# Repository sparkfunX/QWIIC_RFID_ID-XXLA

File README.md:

Sparkfun Qwiic RFID ID-XXLA
========================================

[*SparX Qwiic Keypad (SPX-14867)*](https://www.sparkfun.com/products/14867)

The Qwiic RFID ID-XXLA is a simple board that pairs with the ID-3LA, ID-12LA, ID-20LA, RFID modules. Included with the product is the ID-12LA and three RFID 125Khz cards as a full kit to get you started integrating an I2C RFID solution into your project. Utilizing the onboard ATtiny84A, the Qwiic RFID takes the six byte ID tag of your 125Khz RFID card, attaches a time stamp to it, and puts it onto a stack that holds up to 20 unique RFID scans at any given time. This information is easy to get at with some simple I2C commands and weve included some example code that shows you just how to do it using the broken out interrupt pin. Weve also broken out two antennae pins that should only be used with the smaller ID-3LA.

The Qwiic RFID has a buzzer and LED that indicates that card has been scanned. Weve included a jumper to disconnect the buzzer, a jumper for the I2C pull-up resistors, an interrupt jumper, and finally an address jumper. The Qwiic RFID comes fully decked out in Qwiic connectors, no need to solder a thing, just plug it in and start scanning!

We do not plan to regularly produce SparkX products so get them while theyre hot!

Repository Contents
-------------------

* **/Examples** - A number of examples to show how to read buttons with time, change the I2C address and scan for I2C devices
* **/Firmware** - The core sketch that runs Qwiic RFID ID-XXLA
* **/Hardware** - Eagle design files (.brd, .sch)

License Information
-------------------

This product is _**open source**_! 

Please review the LICENSE.md file for license information. 

If you have any questions or concerns on licensing, please contact techsupport@sparkfun.com.

Please use, reuse, and modify these files as you see fit. Please maintain attribution to SparkFun Electronics and release any derivative under the same license.

Distributed as-is; no warranty is given.

- Your friends at SparkFun.

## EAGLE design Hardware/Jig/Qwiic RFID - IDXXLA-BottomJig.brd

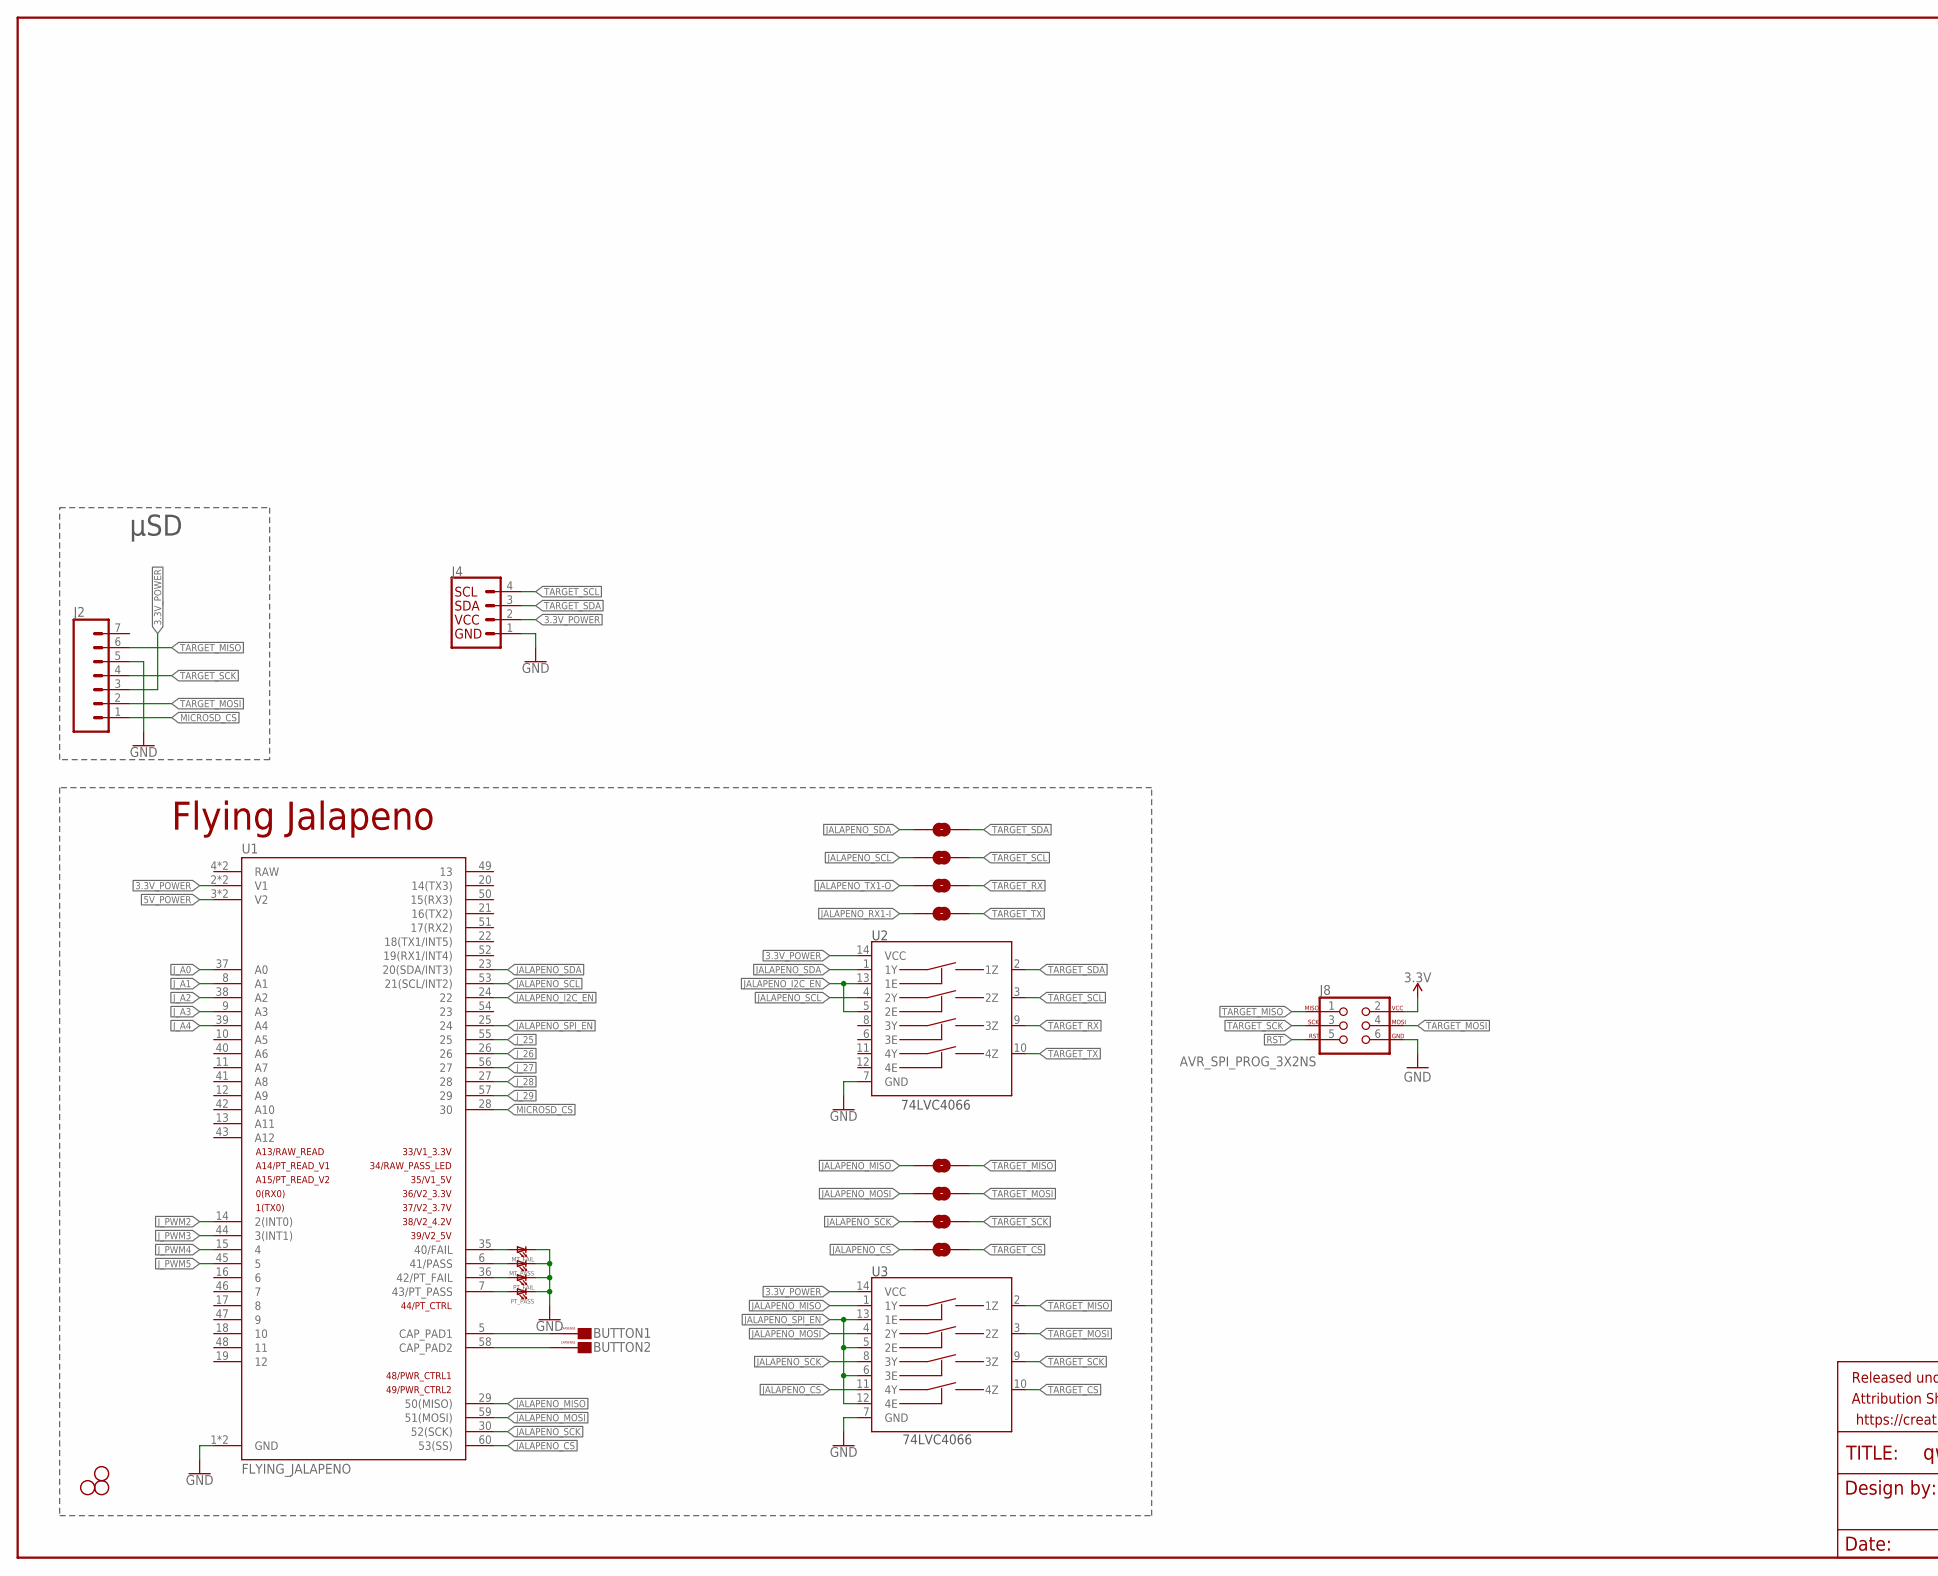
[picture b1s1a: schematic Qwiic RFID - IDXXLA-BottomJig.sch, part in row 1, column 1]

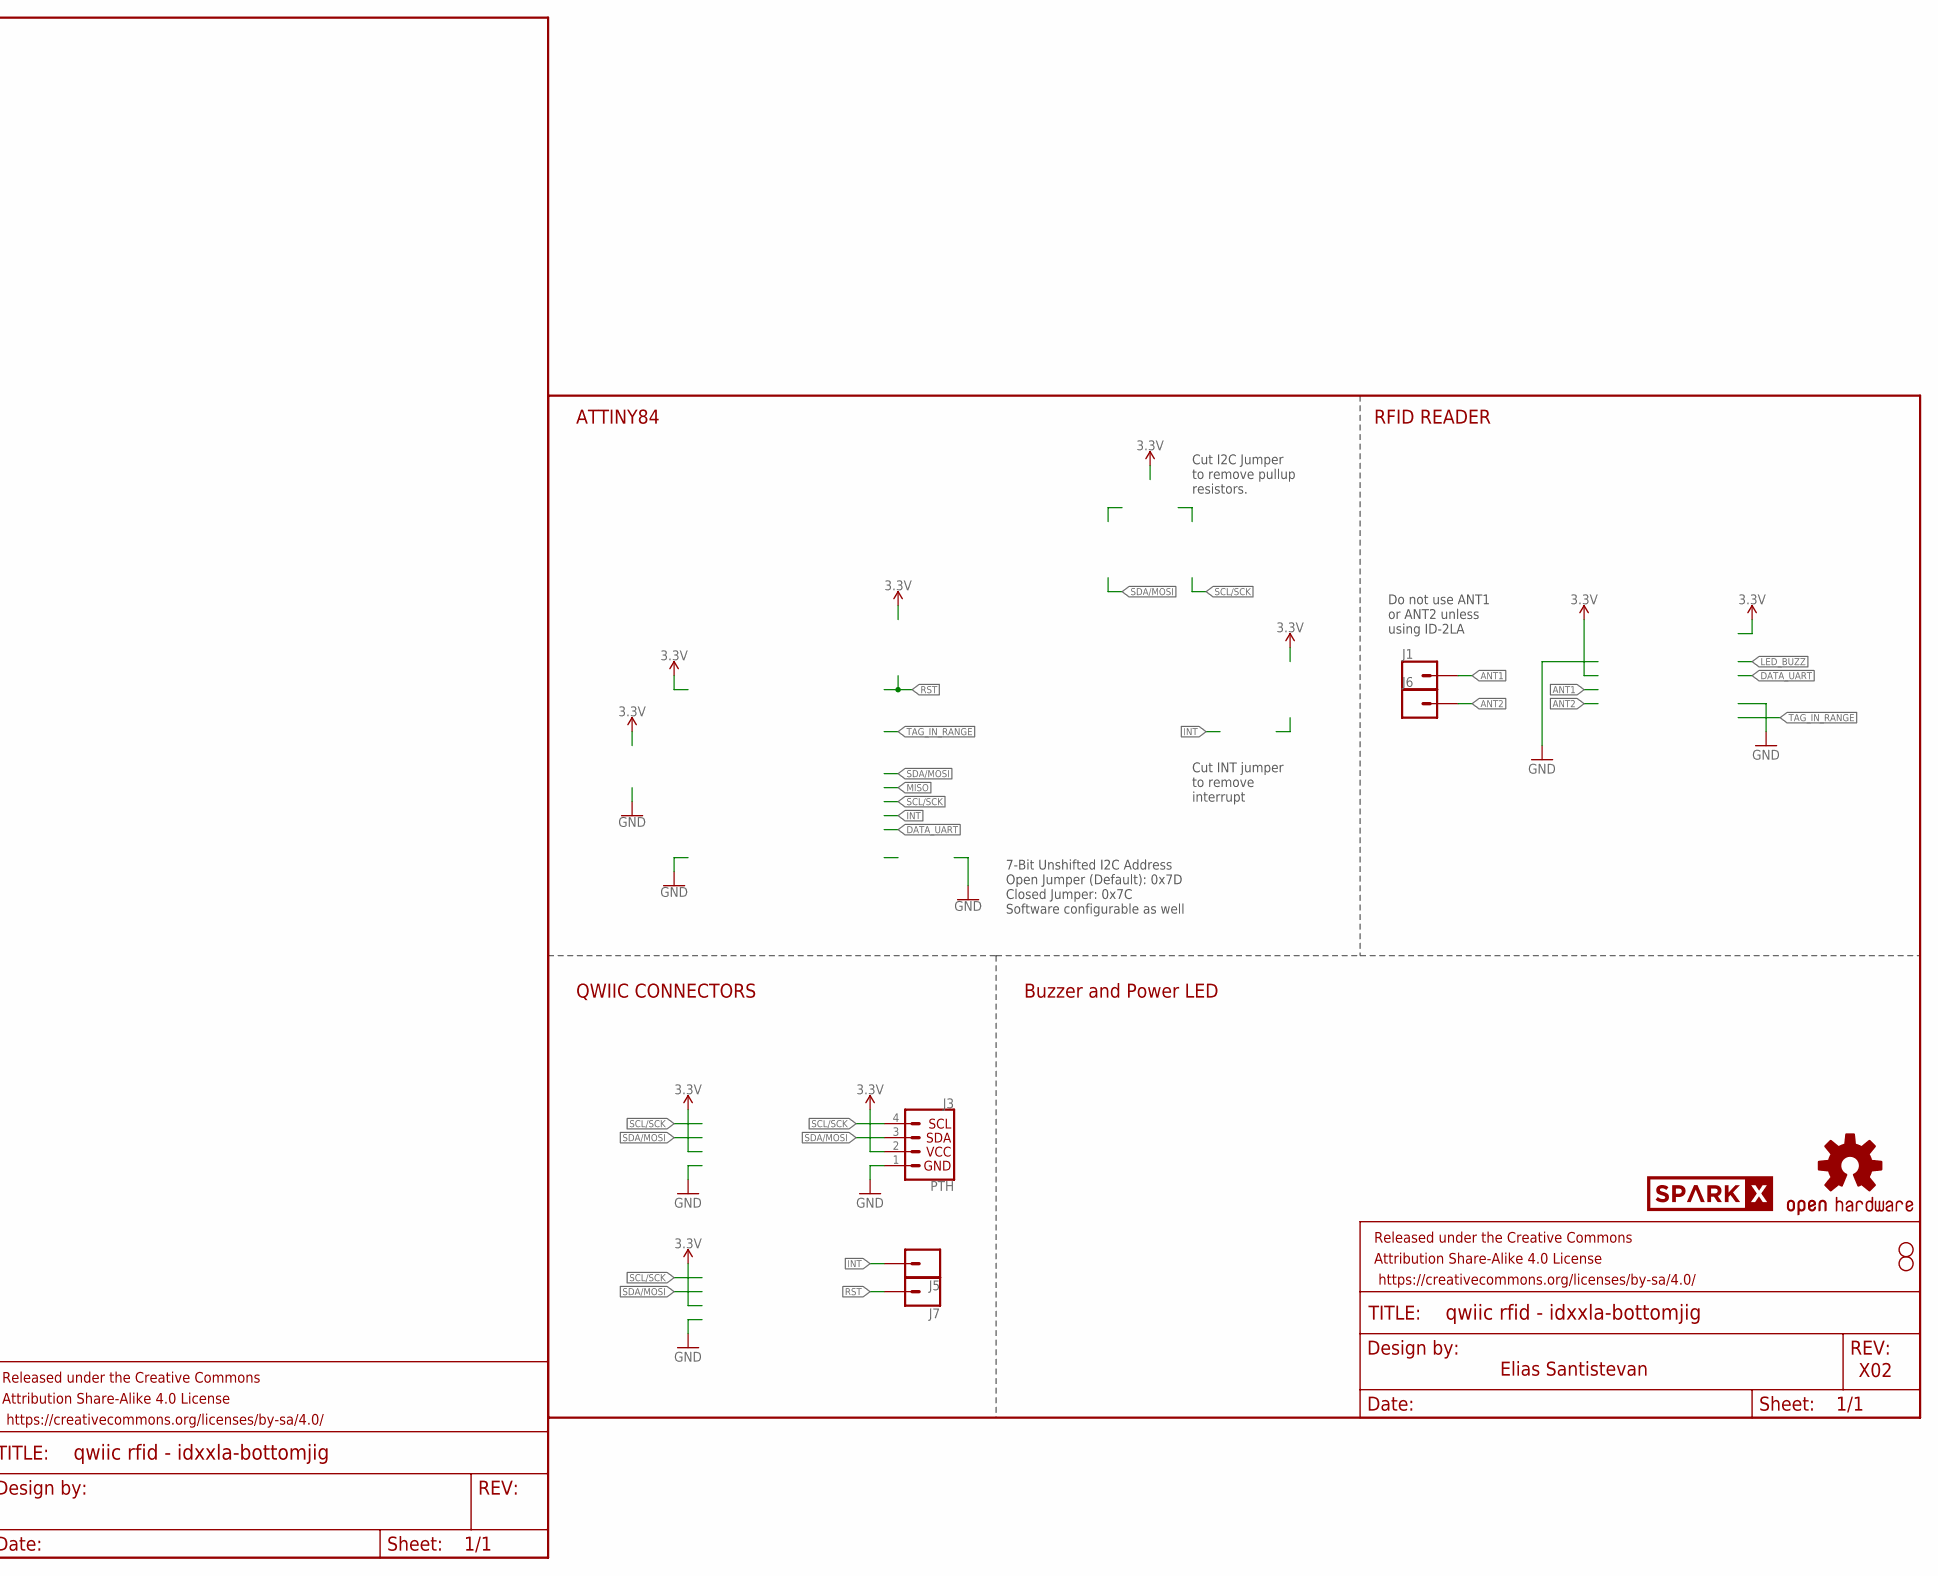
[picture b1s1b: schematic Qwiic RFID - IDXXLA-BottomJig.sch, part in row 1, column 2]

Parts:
BUTTON1, BUTTON2: CAPSENSE_BUTTON_PAD_ONLY; CAPSENSE_BUTTON_PADS_ONLY
FRAME1: FRAME-LETTER; CREATIVE_COMMONS
FRAME2: FRAME-LEDGER; CREATIVE_COMMONS
H1, H3, H4: STAND-OFF
J1, J5, J6, J7: CONN_01PTH_NO_SILK_YES_STOP; 1X01_NO_SILK
J2: CONN_07; 1X07
J3: PTH; 1X04_NO_SILK
J4: QWIIC_CONNECTORJS-1MM; 1X04_1MM_RA
J8: AVR_SPI_PROG_3X2NS; 2X3-NS
JP3, JP4: STAND-OFF
J_SCL, J_SCL1, J_SCL2, J_SCL3, J_SCL4, J_SCL5: JUMPER-SMT_2_NO_NO-SILK; SMT-JUMPER_2_NO_NO-SILK
J_SDA, J_SDA1: JUMPER-SMT_2_NO_NO-SILK; SMT-JUMPER_2_NO_NO-SILK
LOGO1: OSHW-LOGOMINI; OSHW-LOGO-MINI
MT_FAIL: LED1206; LED-1206
MT_PASS: LED1206; LED-1206
PT_FAIL: LED1206; LED-1206
PT_PASS: LED1206; LED-1206
U1: FLYING_JALAPENO; FLYING_JALAPENO_V3_M
U2, U3: 74LVC4066; SO14
U$4: SPARKX-LOGO3; SPARKX-SMALL

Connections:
3.3V: J3.2 (VCC), J8.2
3.3V_POWER: J2.3, J4.2, U1.2 (V1), U1.32 (V1), U2.14 (VCC), U3.14 (VCC)
5V_POWER: U1.3 (V2), U1.33 (V2)
!INT: J5.1
!RST: J7.1, J8.5
ANT1: J1.1
ANT2: J6.1
BUTTON1: BUTTON1.CAPSENSE_PAD, U1.5 (CAP_PAD1)
BUTTON2: BUTTON2.CAPSENSE_PAD, U1.58 (CAP_PAD2)
GND: J2.5, J3.1 (GND), J4.1, J8.6, MT_FAIL.C, MT_PASS.C, PT_FAIL.C, PT_PASS.C, U1.1 (GND), U1.31 (GND), U2.7 (GND), U3.7 (GND)
JALAPENO_CS: J_SDA1.1, U1.60 (53(SS)), U3.11 (4Y)
JALAPENO_I2C_EN: U1.24 (22), U2.5 (2E), U2.13 (1E)
JALAPENO_MISO: J_SCL5.1, U1.29 (50(MISO)), U3.1 (1Y)
JALAPENO_MOSI: J_SCL3.1, U1.59 (51(MOSI)), U3.4 (2Y)
JALAPENO_RX1-I: J_SDA.1
JALAPENO_SCK: J_SCL4.1, U1.30 (52(SCK)), U3.8 (3Y)
JALAPENO_SCL: J_SCL.1, U1.53 (21(SCL/INT2)), U2.4 (2Y)
JALAPENO_SDA: J_SCL2.1, U1.23 (20(SDA/INT3)), U2.1 (1Y)
JALAPENO_SPI_EN: U1.25 (24), U3.5 (2E), U3.6 (3E), U3.12 (4E), U3.13 (1E)
JALAPENO_TX1-O: J_SCL1.1
J_25: U1.55 (25)
J_26: U1.26
J_27: U1.56 (27)
J_28: U1.27 (28)
J_29: U1.57 (29)
J_A0: U1.37 (A0)
J_A1: U1.8 (A1)
J_A2: U1.38 (A2)
J_A3: U1.9 (A3)
J_A4: U1.39 (A4)
J_PWM2: U1.14 (2(INT0))
J_PWM3: U1.44 (3(INT1))
J_PWM4: U1.15 (4)
J_PWM5: U1.45 (5)
MICROSD_!CS!: J2.1, U1.28 (30)
MT_FAIL: MT_FAIL.A, U1.35 (40/FAIL)
MT_PASS: MT_PASS.A, U1.6 (41/PASS)
PT_FAIL: PT_FAIL.A, U1.36 (42/PT_FAIL)
PT_PASS: PT_PASS.A, U1.7 (43/PT_PASS)
SCL/SCK: J3.4 (SCL)
SDA/MOSI: J3.3 (SDA)
TARGET_CS: J_SDA1.2, U3.10 (4Z)
TARGET_MISO: J2.6, J8.1, J_SCL5.2, U3.2 (1Z)
TARGET_MOSI: J2.2, J8.4, J_SCL3.2, U3.3 (2Z)
TARGET_RX: J_SCL1.2, U2.9 (3Z)
TARGET_SCK: J2.4, J8.3, J_SCL4.2, U3.9 (3Z)
TARGET_SCL: J4.4, J_SCL.2, U2.3 (2Z)
TARGET_SDA: J4.3, J_SCL2.2, U2.2 (1Z)
TARGET_TX: J_SDA.2, U2.10 (4Z)

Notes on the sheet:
X02
Buzzer and Power LED
RFID READER
ATTINY84
QWIIC CONNECTORS
Elias Santistevan
7-Bit Unshifted I2C Address Open Jumper (Default): 0x7D Closed Jumper: 0x7C Software configurable as well
Cut INT jumper to remove interrupt
Cut I2C Jumper to remove pullup resistors.
Do not use ANT1 or ANT2 unless using ID-2LA
Flying Jalapeno
μSD

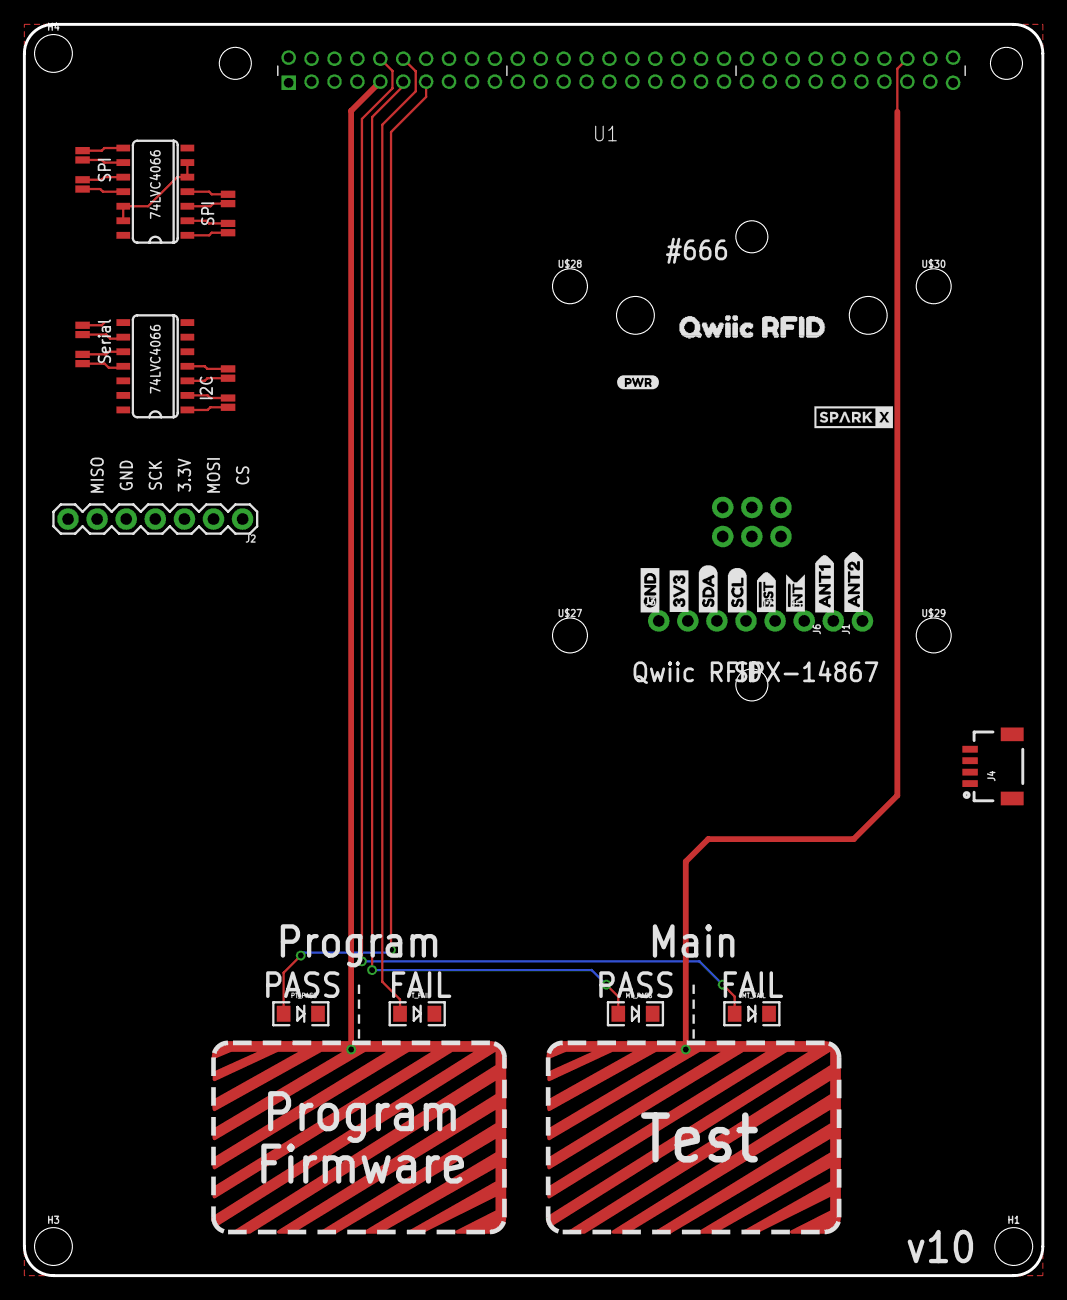
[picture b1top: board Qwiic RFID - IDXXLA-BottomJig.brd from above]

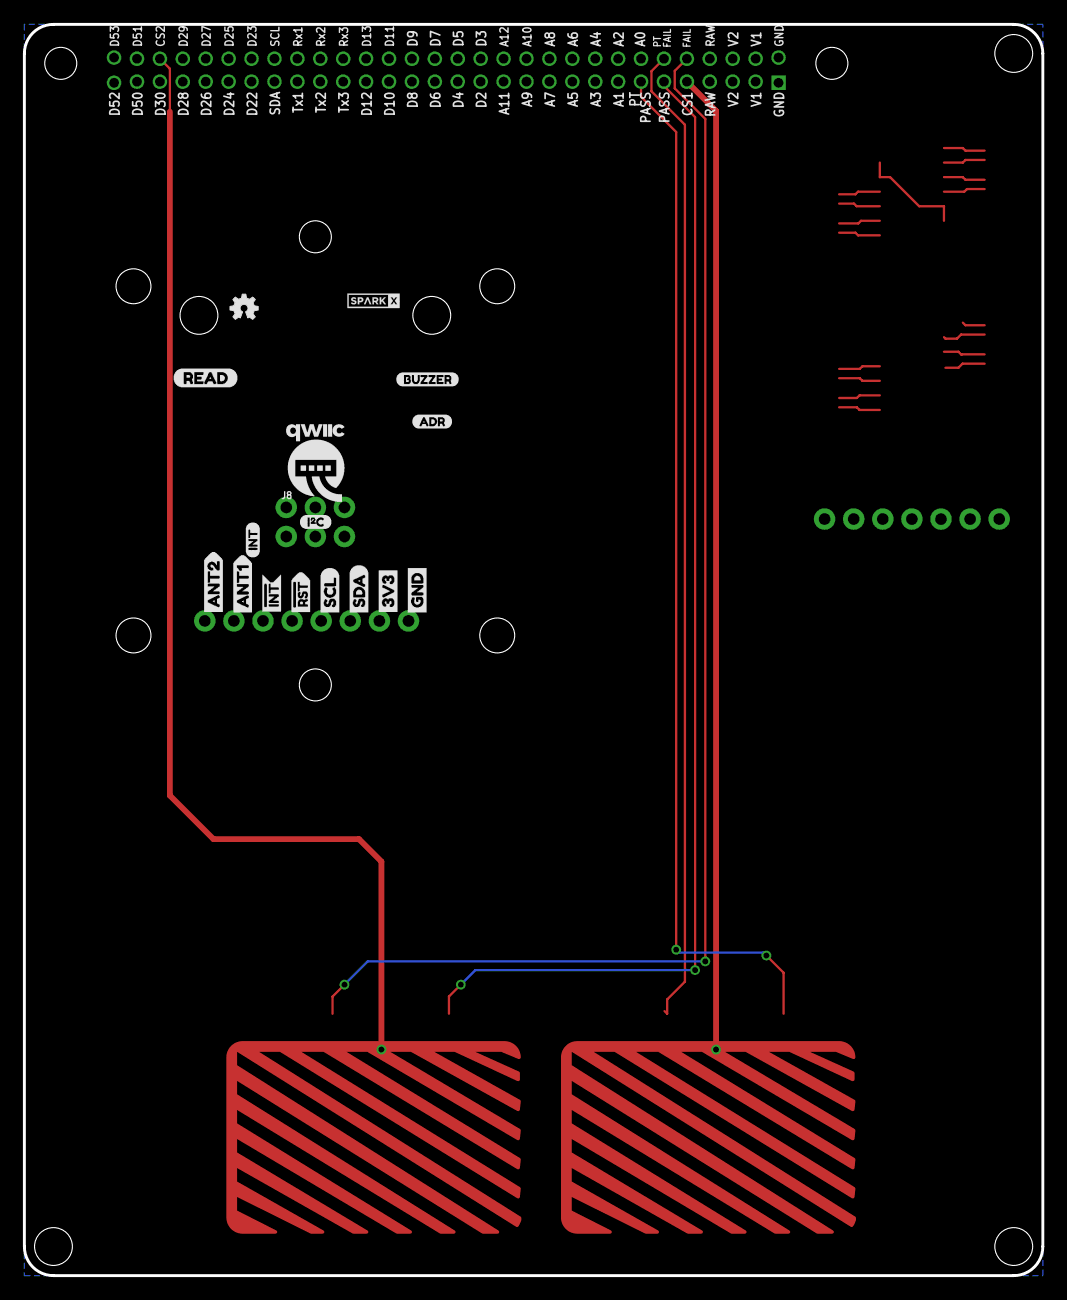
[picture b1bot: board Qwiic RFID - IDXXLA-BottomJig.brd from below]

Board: 2 copper layers, 88.9 x 109.2 mm, 65 parts (17 on the bottom side), 28 nets.

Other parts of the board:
U$1: SPARKX-TINY
U$2: I_SUPER2_C-()-03
U$3, U$17: ANT20
U$5, U$26: RST#-[>
U$6, U$23: SDA-[)
U$7, U$22: SCL-[)
U$8: QWIIC-LOGO-MEDIUM
U$9, U$25: GND-04
U$10, U$24: 3V3-04
U$11, U$21: INT#-[<
U$12: ADR0
U$13: INT0
U$14: PWR-()-03
U$15: BUZZER0
U$16, U$20: ANT10
U$18: READ0
U$19: QWIIC_RFID0
U$27, U$28, U$29, U$30: STAND-OFF-TIGHT
U$31, U$32: NUBBIN_LOCKER

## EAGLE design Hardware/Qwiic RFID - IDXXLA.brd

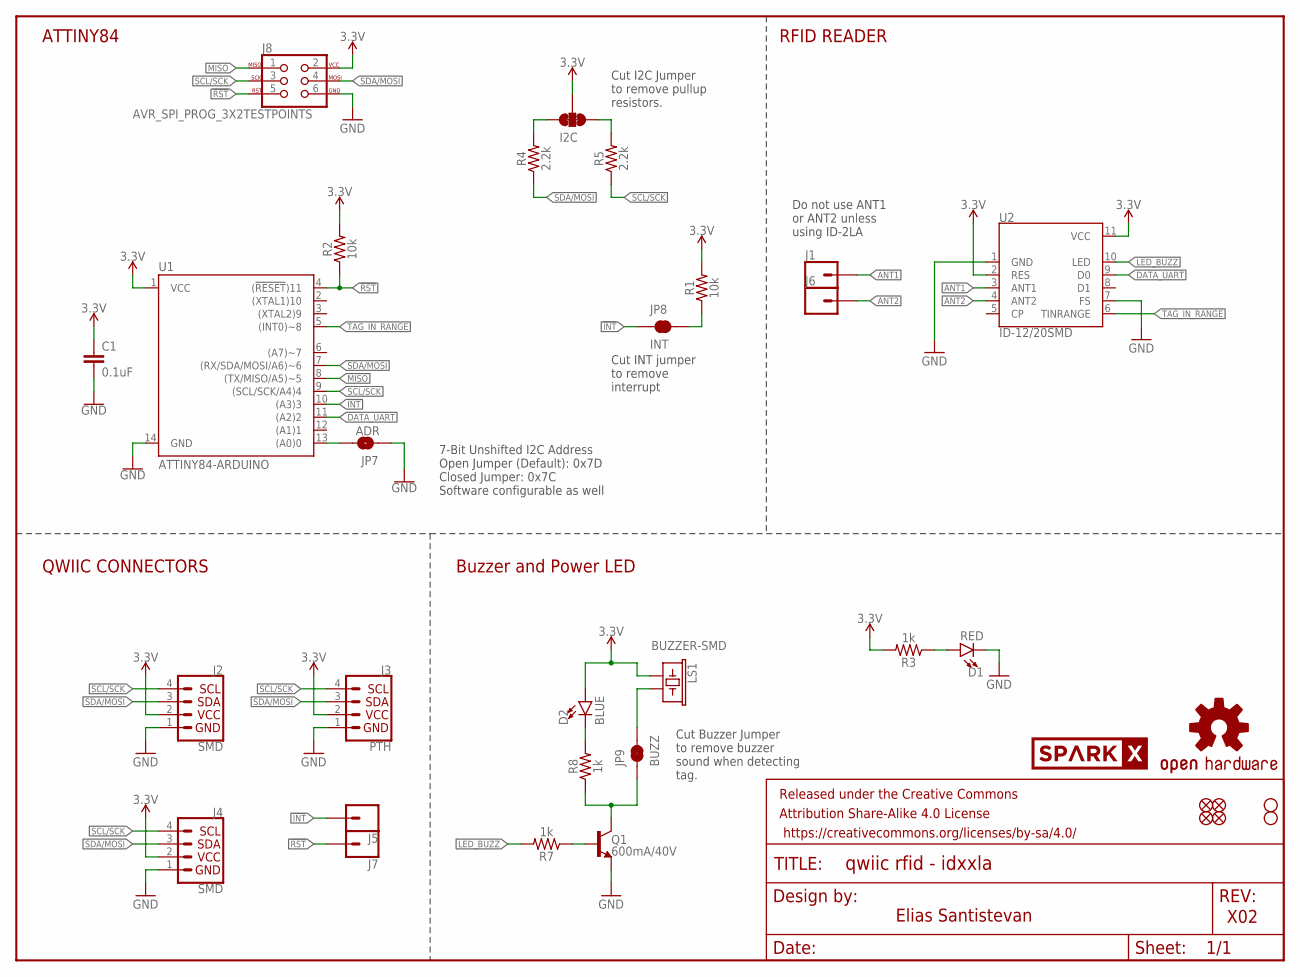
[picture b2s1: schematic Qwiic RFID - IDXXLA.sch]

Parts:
C1: 0.1uF; 0603
D1: RED; LED-0603
D2: BLUE; LED-0603
FRAME1: FRAME-LETTER; CREATIVE_COMMONS
I2C: JUMPER-SMT_3_2-NC_TRACE_SILK; SMT-JUMPER_3_2-NC_TRACE_SILK
J1, J5, J6, J7: CONN_01PTH_NO_SILK_YES_STOP; 1X01_NO_SILK
J2, J4: SMD; 1X04_1MM_RA
J3: PTH; 1X04_NO_SILK
J8: AVR_SPI_PROG_3X2TESTPOINTS; 2X3_TEST_POINTS
JP1, JP2, JP5, JP6: FIDUCIALUFIDUCIAL; MICRO-FIDUCIAL
JP3, JP4: STAND-OFF
JP7: ADR; SMT-JUMPER_2_NO_SILK
JP8: INT; SMT-JUMPER_2_NC_TRACE_SILK
JP9: BUZZ; SMT-JUMPER_2_NC_TRACE_SILK
LOGO1: OSHW-LOGOMINI; OSHW-LOGO-MINI
LS1: BUZZER-SMD; BUZZER-CCV
Q1: 600mA/40V; SOT23-3
R1, R2: 10k; 0603
R3, R7, R8: 1k; 0603
R4, R5: 2.2k; 0603
U1: ATTINY84-ARDUINO; SO14
U2: ID-12/20SMD; ID-12_SMD
U$4: SPARKX-LOGO3; SPARKX-SMALL

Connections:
3.3V: C1.1, D2.A, I2C.2, J2.2 (VCC), J3.2 (VCC), J4.2 (VCC), J8.2, LS1.+ (1), R1.2, R2.2, R3.2, U1.1 (VCC), U2.2 (RES), U2.11 (VCC)
!INT: J5.1, JP8.1, U1.10 ((A3)3)
!RST: J7.1, J8.5, R2.1, U1.4 ((!RESET!)11)
ANT1: J1.1, U2.3 (ANT1)
ANT2: J6.1, U2.4 (ANT2)
DATA_UART: U1.11 ((A2)2), U2.9 (D0)
GND: C1.2, D1.C, J2.1 (GND), J3.1 (GND), J4.1 (GND), J8.6, JP7.1, Q1.2 (E), U1.14 (GND), U2.1 (GND), U2.7 (FS)
LED_BUZZ: R7.2, U2.10 (LED)
MISO: J8.1, U1.8 ((TX/MISO/A5)~5)
unnamed: I2C.1, R5.2
unnamed: I2C.3, R4.2
unnamed: D1.A, R3.1
unnamed: JP8.2, R1.1
unnamed: D2.C, R8.2
unnamed: JP7.2, U1.13 ((A0)0)
unnamed: Q1.1 (B), R7.1
unnamed: JP9.1, Q1.3 (C), R8.1
unnamed: JP9.2, LS1.- (2)
SCL/SCK: J2.4 (SCL), J3.4 (SCL), J4.4 (SCL), J8.3, R5.1, U1.9 ((SCL/SCK/A4)4)
SDA/MOSI: J2.3 (SDA), J3.3 (SDA), J4.3 (SDA), J8.4, R4.1, U1.7 ((RX/SDA/MOSI/A6)~6)
TAG_IN_RANGE: U1.5 ((INT0)~8), U2.6 (TINRANGE)

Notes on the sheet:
X02
Buzzer and Power LED
RFID READER
ATTINY84
QWIIC CONNECTORS
Elias Santistevan
7-Bit Unshifted I2C Address Open Jumper (Default): 0x7D Closed Jumper: 0x7C Software configurable as well
Cut Buzzer Jumper to remove buzzer sound when detecting tag.
Cut INT jumper to remove interrupt
Cut I2C Jumper to remove pullup resistors.
Do not use ANT1 or ANT2 unless using ID-2LA

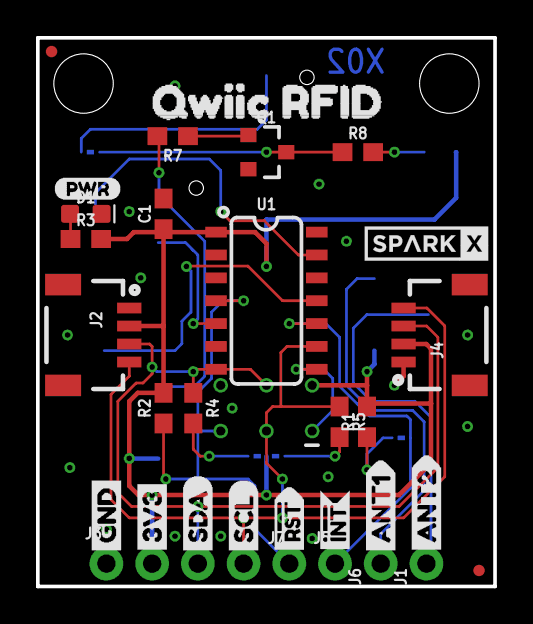
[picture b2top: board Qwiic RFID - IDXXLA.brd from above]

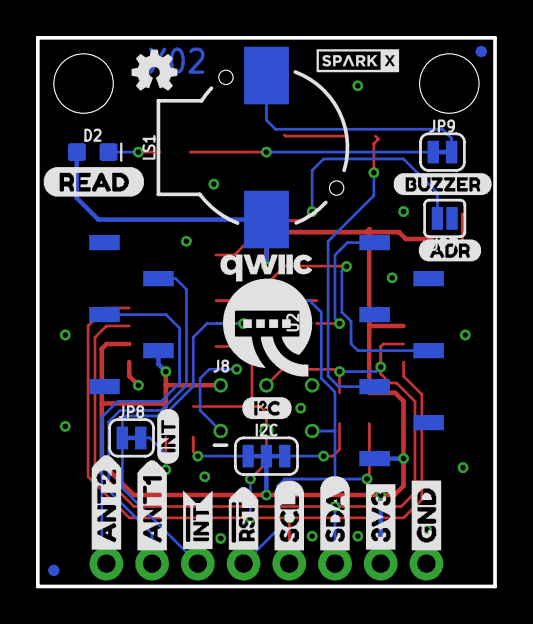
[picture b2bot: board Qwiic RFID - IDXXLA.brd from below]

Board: 2 copper layers, 25.4 x 30.5 mm, 60 parts (26 on the bottom side), 21 nets.

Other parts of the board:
U$1: SPARKX-TINY
U$2: I_SUPER2_C-()-03
U$3, U$17: ANT20
U$5, U$26: RST#-[>
U$6, U$23: SDA-[)
U$7, U$22: SCL-[)
U$8: QWIIC-LOGO-MEDIUM
U$9, U$25: GND-04
U$10, U$24: 3V3-04
U$11, U$21: INT#-[<
U$12: ADR0
U$13: INT0
U$14: PWR-()-03
U$15: BUZZER0
U$16, U$20: ANT10
U$18: READ0
U$19: QWIIC_RFID0

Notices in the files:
parts and their libraries:
SparkFun-Connectors: Licensing: Creative Commons ShareAlike 4.0 International - https://creativecommons.org/licenses/by-sa/4.0
SparkFun-Aesthetics: Released under the Creative Commons Attribution Share-Alike 4.0 License
SparkFun-Aesthetics: https://creativecommons.org/licenses/by-sa/4.0
